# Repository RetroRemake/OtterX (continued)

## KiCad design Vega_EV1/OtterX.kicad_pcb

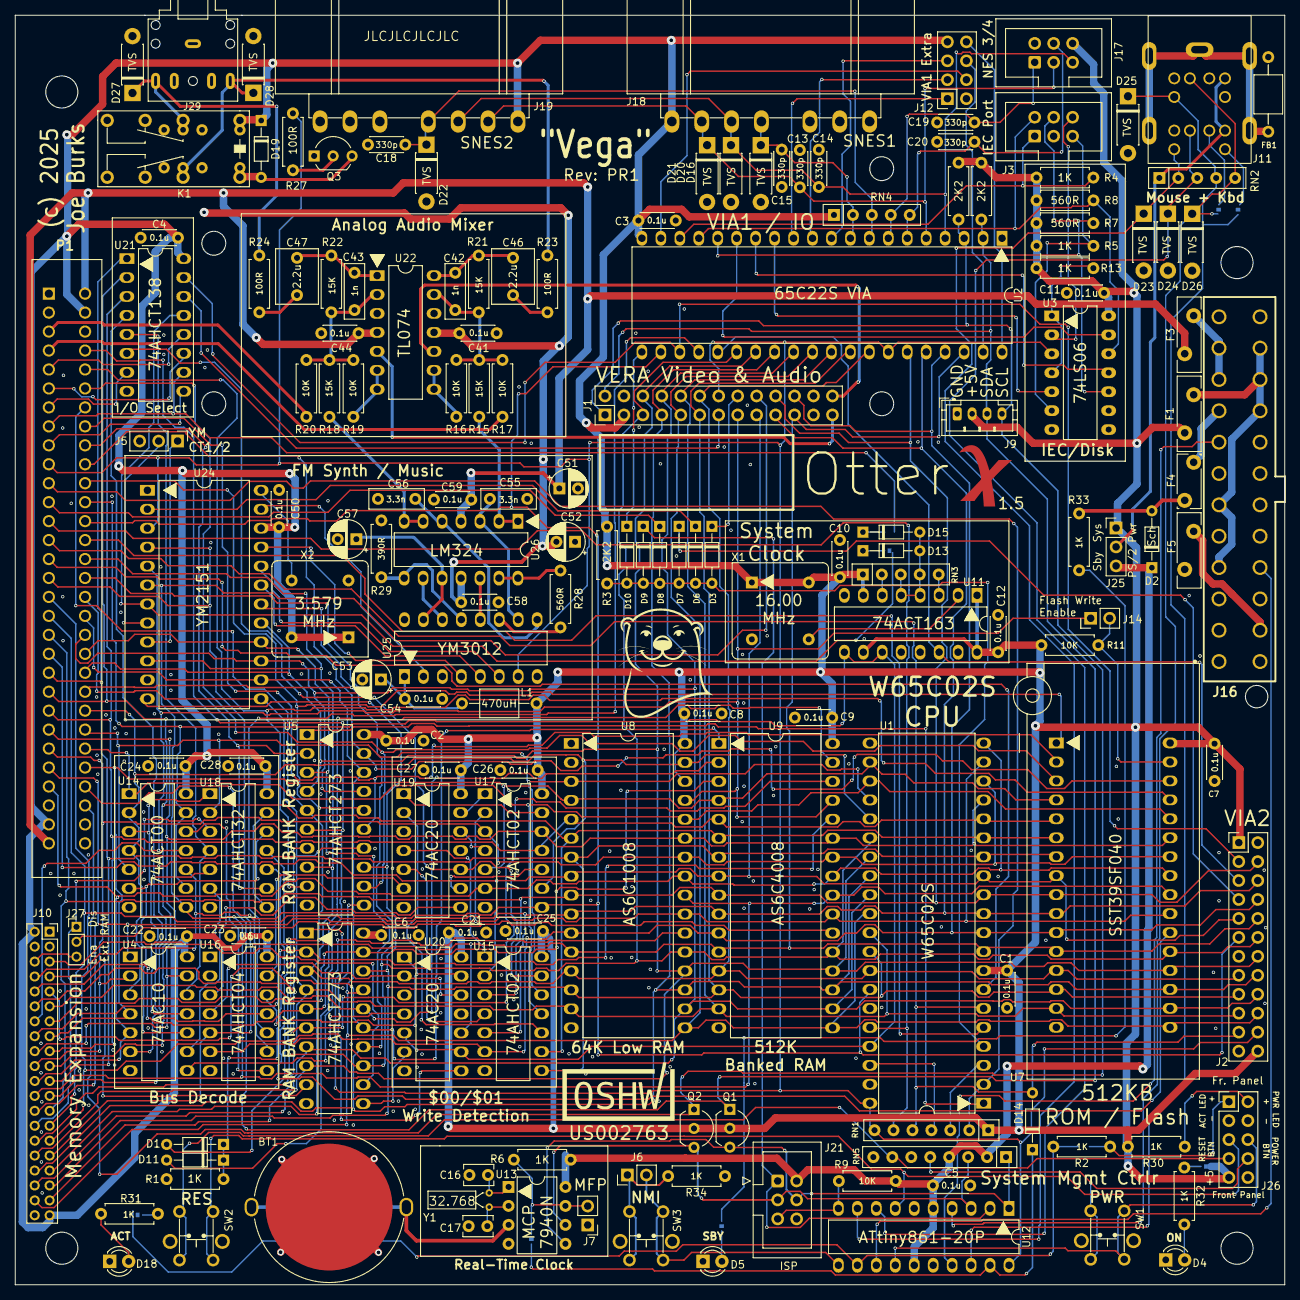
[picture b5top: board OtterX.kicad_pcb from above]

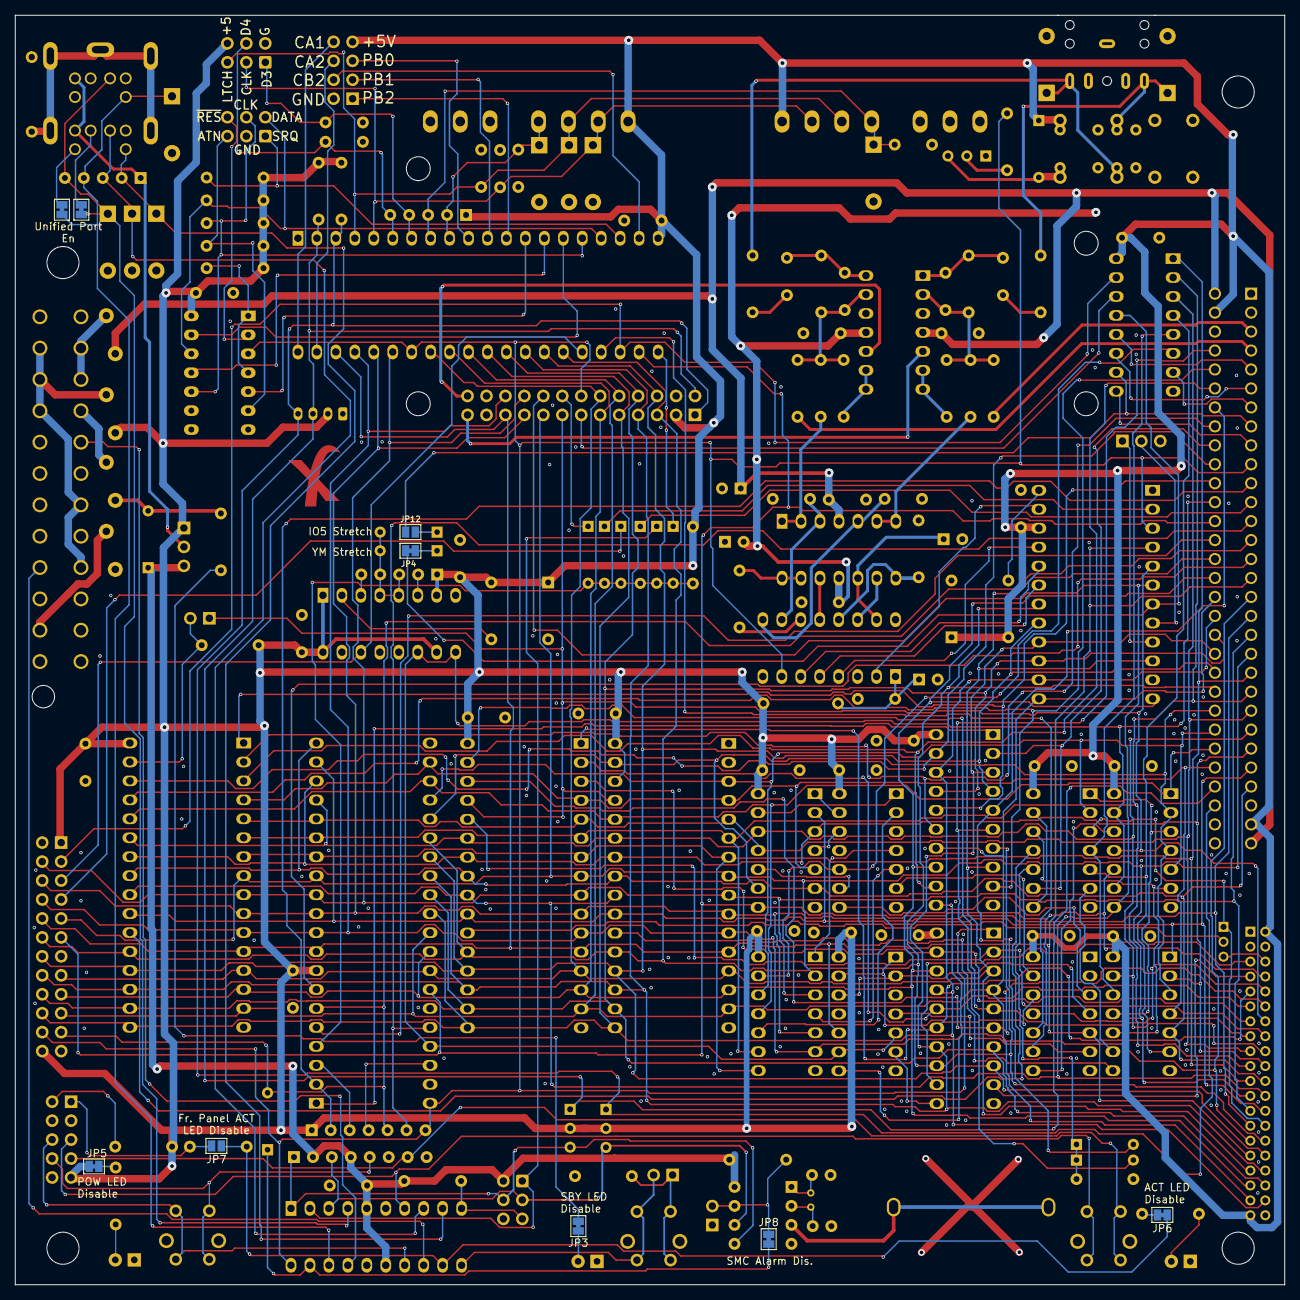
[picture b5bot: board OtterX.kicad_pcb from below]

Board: 4 copper layers, 170.1 x 170.1 mm, 185 parts (9 on the bottom side), 205 nets.

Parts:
BT1: BAT-HLD-001-THM; AliEx_BatClip
C1, C2, C3, C4, C5, C6, C7, C8, C9, C10, C11, C12, C21, C22, C23, C24, C25, C26, C27, C28, C41, C44, C50, C54, C58, C59: 0.1u; C_Disc_D4.3mm_W1.9mm_P5.00mm
C13, C14, C15, C18, C19, C20: 330p; C_Disc_D4.3mm_W1.9mm_P5.00mm
C16, C17: 3p; C_Disc_D3.8mm_W2.6mm_P2.50mm
C42, C43: 1n; C_Rect_L7.2mm_W2.5mm_P5.00mm_FKS2_FKP2_MKS2_MKP2
C46, C47: 2.2u; C_Rect_L7.2mm_W5.5mm_P5.00mm_FKS2_FKP2_MKS2_MKP2
C51, C52, C53, C57: 10u; CP_Radial_D5.0mm_P2.50mm
C55, C56: 3.3n; C_Rect_L7.2mm_W2.5mm_P5.00mm_FKS2_FKP2_MKS2_MKP2
D1, D3, D6, D7, D8, D9, D10, D11, D13, D14, D15, D19: 1N4148; D_DO-34_SOD68_P7.62mm_Horizontal
D2: 1N5819; D_DO-34_SOD68_P7.62mm_Horizontal
D4: LED_GRN; LED_D3.0mm
D5: LED_YEL; LED_D3.0mm
D16, D20, D21, D22, D23, D24, D25, D26, D27, D28: P4KE6.8CA; D_DO-41_SOD81_P7.62mm_Horizontal
D18: LED_RED; LED_D3.0mm
F1: JK30; Fuse_Bourns_MF-RG400
F3: RXEF110; Fuse_Bourns_MF-RG400
F4: RXEF025; Fuse_Bourns_MF-RG300
F5: RXEF010; Fuse_Bourns_MF-RG400
FB1: FerriteBead_Small; L_Axial_L5.0mm_D3.6mm_P10.00mm_Horizontal_Murata_BL01RN1A2A2
H1, H2, H3, H4: MountingHole; MountingHole_3.2mm_M3
H5, H6, H7, H8: MountingHole; MountingHole_4.3mm_M4
J1: VERA_CONN; PinHeader_2x13_P2.54mm_Vertical
J2: VIA2 Header; PinHeader_2x12_P2.54mm_Vertical
J3, J17, J21: IDC_2x03; IDC-Header_2x03_P2.54mm_Vertical
J5: YM CT Out; PinHeader_1x03_P2.54mm_Vertical
J6: Ext. NMI; PinHeader_1x02_P2.54mm_Vertical
J7: RTC GPIO; PinHeader_1x02_P2.54mm_Vertical
J9: I2C; JST_PH_B4B-PH-K_1x04_P2.00mm_Vertical
J10: 1.5MB RAM Expansion; PinSocket_2x20_P2.00mm_Vertical
J11: KMDGX-6SG; Kycon KMDGX-6SG P-S4N
J12: VIA1 Extra Pins; PinSocket_2x04_P2.54mm_Vertical
J14: Flash WR EN; PinHeader_1x02_P2.54mm_Vertical
J16: ATX-24; 1-1775099-3-Fixed
J18: SNES0; SNES_L
J19: SNES1; SNES_R
J25: PS2 Pwr Src; PinHeader_1x03_P2.54mm_Vertical
J26: Front Panel; PinHeader_2x05_P2.54mm_Vertical
J27: EXTRAM_ENABLE; PinHeader_1x03_P2.00mm_Vertical
J29: AudioPlug3; Jack_3.5mm_CUI_SJ1-3525N_Horizontal
JP1: SinglePS2_CLK; SolderJumper-2_P1.3mm_Bridged_Pad1.0x1.5mm
JP2: SinglePS2_DAT; SolderJumper-2_P1.3mm_Bridged_Pad1.0x1.5mm
JP3: SBY LED Disable; SolderJumper-2_P1.3mm_Bridged_Pad1.0x1.5mm
JP4: SolderJumper_2_Bridged; SolderJumper-2_P1.3mm_Bridged_Pad1.0x1.5mm
JP5: Pow LED Disable; SolderJumper-2_P1.3mm_Bridged_Pad1.0x1.5mm
JP6: Act LED Disable; SolderJumper-2_P1.3mm_Bridged_Pad1.0x1.5mm
JP7: ACT LED Bypass; SolderJumper-2_P1.3mm_Open_Pad1.0x1.5mm
JP8: SMC Alarm; SolderJumper-2_P1.3mm_Bridged_Pad1.0x1.5mm
JP12: IO3 Clk Stretch; SolderJumper-2_P1.3mm_Open_Pad1.0x1.5mm
K1: HK19F; HK19F-DPDT-Relay
L1: 470uH; L_Axial_L5.0mm_D3.6mm_P10.00mm_Horizontal_Murata_BL01RN1A2A2
P1: 60 Pin Edge Conn; TE155308438
Q1, Q2, Q3: 2N7000; TO-92_Inline_Wide
R1, R2, R4, R5, R6, R13, R30, R31, R32, R33, R34: 1K; R_Axial_DIN0207_L6.3mm_D2.5mm_P7.62mm_Horizontal
R3, R10, R12: 2K2; R_Axial_DIN0207_L6.3mm_D2.5mm_P7.62mm_Horizontal
R7, R8, R28: 560R; R_Axial_DIN0207_L6.3mm_D2.5mm_P7.62mm_Horizontal
R9, R11, R16, R17, R19, R20: 10K; R_Axial_DIN0207_L6.3mm_D2.5mm_P7.62mm_Horizontal
R15, R18, R21, R22: 15K; R_Axial_DIN0207_L6.3mm_D2.5mm_P7.62mm_Horizontal
R23, R24, R27: 100R; R_Axial_DIN0207_L6.3mm_D2.5mm_P7.62mm_Horizontal
R29: 390R; R_Axial_DIN0207_L6.3mm_D2.5mm_P7.62mm_Horizontal
RN1: 2K2; R_Array_SIP7
RN2, RN3: 2K2; R_Array_SIP5
RN4: 3K3; R_Array_SIP5
RN5: 2K2; R_Array_SIP8
SW1, SW2, SW3: FSM4JH; Tactile Switch Dual
U1: W65C816S; DIP-40_W15.24mm-ShortWidePads_1mmDrill
U2: W65C22S; DIP-40_W15.24mm-ShortWidePads_1mmDrill
U3: 74LS06; DIP-14_W7.62mm_ShortWidePads
U4: 74AC10; DIP-14_W7.62mm_ShortWidePads_Drill1mm
U5, U6: 74AHCT273; DIP-20_W7.62mm_ShortWidePads_1mmDrill
U7: SST39SF040; DIP_Socket-32_W11.9_W12.7_W15.24_W17.78_W18.5_3M_232-1285-0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
U8: AS6C1008-55PCN; DIP-32_W15.24mm_ShortWidePads_1mmDrill
U9: AS6C4008-55PCN; DIP-32_W15.24mm_ShortWidePads_1mmDrill
U11: 74ACT163; DIP-16_W7.62mm_ShortWidePads_1mmDrill
U12: ATtiny861-20P; DIP-20_W7.62mm_ShortWidePads_1mmDrill
U13: MCP7940N-xP; DIP-8_W7.62mm
U14: 74ACT00; DIP-14_W7.62mm_ShortWidePads_Drill1mm
U15, U17: 74AHCT02; DIP-14_W7.62mm_ShortWidePads_Drill1mm
U16: 74AHCT04; DIP-14_W7.62mm_ShortWidePads_Drill1mm
U18: 74AHCT32; DIP-14_W7.62mm_ShortWidePads_Drill1mm
U19, U20: 74AC20; DIP-14_W7.62mm_ShortWidePads_Drill1mm
U21: 74AHCT138; DIP-16_W7.62mm_ShortWidePads_1mmDrill
U22: TL074; DIP-14_W7.62mm_ShortWidePads_Drill1mm
U24: YM2151; DIP-24_W15.24mm_ShortWidePads_1mmDrill
U25: YM3012; DIP-16_W7.62mm_ShortWidePads_1mmDrill
U26: LM324; DIP-14_W7.62mm_ShortWidePads_Drill1mm
X1: ACH-16.000MHZ-EK; Oscillator_DIP-8
X2: ECS-2100AX-3.579545MHZ; Oscillator_DIP-8
Y1: ECS-.327-6-13X; Crystal_DS26_D2.0mm_L6.0mm_Horizontal

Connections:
+5V: C1.2, C2.2, C3.2, C4.2, C6.2, C7.2, C8.2, C9.2, C10.2, C11.2, C12.1, C21.1, C22.1, C23.1, C24.1, C25.1, C26.1, C27.1, C28.1, C50.2, D19.1 (K), F1.2, J1.3, J2.1, J2.24, J9.2, J10.2, J10.39, J12.7, J17.6, J18.1, J19.1, J25.1, J26.9, JP5.1 (A), K1.16, L1.1, P1.4 (VCC), P1.57 (VCC), Q1.2 (G), Q2.2 (G), R3.1, R4.1, R5.1, R7.1, R8.1, R10.1, R11.1, R12.1, R13.1, R30.2, RN1.1 (common), RN3.1 (common), RN4.1 (common), U1.8 (VDD), U2.20 (VCC), U3.14 (VCC), U4.14 (VCC), U5.20 (VCC), U6.20 (VCC), U7.32 (VCC), U8.30 (CE2), U8.32 (VCC), U9.32 (VCC), U11.1 (~MR), U11.7 (CEP), U11.10 (CET), U11.16 (VCC), U14.14 (VCC), U15.14 (VCC), U16.14 (VCC), U17.14 (VCC), U18.14 (VCC), U19.14 (VCC), U20.14 (VCC), U21.16 (VCC), U24.22 (Vcc), X1.1 (EN), X1.8 (Vcc), X2.1 (EN), X2.8 (Vcc)
+5VSB: C5.2, D2.1 (K), J21.2, J25.3, R6.2, R9.2, RN5.2 (R1.2), RN5.4 (R2.2), U12.5 (VCC), U12.15 (AVCC), U13.8 (VCC)
+5VSB_NOBF: D2.2 (A), F4.1, R33.1
+12V: C44.2, C51.1, C59.2, F3.1, P1.2 (+12V), P1.59 (+12V), U22.4 (V+), U26.4 (V+)
-12V: C41.2, C52.2, C58.2, F5.1, P1.1 (-12V), P1.60 (-12V), U22.11 (V-), U26.11 (V-)
/Audio/Audio Mixer/L_MIX: C43.1, R18.2, R19.2, R20.2, R22.1, U22.2 (-)
/Audio/Audio Mixer/L_P_FILT: C43.2, C47.1, R22.2, U22.1
/Audio/Audio Mixer/R_MIX: C42.1, R15.2, R16.2, R17.2, R21.1, U22.13 (-)
/Audio/Audio Mixer/R_P_FILT: C42.2, C46.1, R21.2, U22.14
/Audio/SH1: U24.20 (SH1), U25.6 (SH1)
/Audio/SH2: U24.19 (SH2), U25.5 (SH2)
/Audio/SO: U24.21 (SO), U25.4 (DATA)
/Audio/YMANL_5V: C53.1, C54.2, L1.2, U25.1 (Vcc)
/Audio/YMANL_CH1: C56.1, U25.9 (CH2), U26.5 (+)
/Audio/YMANL_CH2: C55.1, U25.10 (CH1), U26.3 (+)
/Audio/YMSAMP_OUT: U25.12 (T-BUF(A-OUT)), U26.12 (+)
/Audio/YMVREF_BIAS: C57.1, U25.15 (RB(BIAS)), U26.10 (+)
/Audio/YMVREF_IN: R29.1, U25.13 (MP(V/2)), U26.8
/Audio/YMVREF_OUT: U25.14 (BC(V/2)), U26.9 (-)
/Audio/YM_CLK: U24.24 (phM), X2.5 (OUT)
/Audio/YM_CLK2: U24.23 (phi1), U25.2 (phi1)
/Audio/YM_COM: R28.2, U25.11 (COM(A-IN))
/Audio/YM_CT1: J5.2, U24.8 (CT1)
/Audio/YM_CT2: J5.1, U24.9 (CT2)
/BusDecoder/~ROMENL: U4.10, U14.6, U18.12
/CLK16: U11.2 (CP), X1.5 (OUT)
/IECATT: J3.5, R5.2, U3.6
/IECSRQ: J3.1, R4.2, U2.18 (CB1)
/Memory/RAMBA13: J10.16, U6.2 (Q0), U9.28 (A13)
/Memory/RAMBA14: J10.13, U6.19 (Q7), U9.3 (A14)
/Memory/RAMBA15: J10.10, U6.5 (Q1), U9.31 (A15)
/Memory/RAMBA16: J10.11, U6.16 (Q6), U9.2 (A16)
/Memory/RAMBA17: J10.12, U6.6 (Q2), U9.30 (A17)
/Memory/RAMBA18: J10.9, U6.15 (Q5), U9.1 (A18)
/Memory/RAMBA19: J10.7, U6.9 (Q3)
/Memory/RAMBA20: J10.5, U6.12 (Q4)
/Memory/ROMBA14: P1.10 (ROMB0), U5.9 (Q3), U7.29 (A14)
/Memory/ROMBA15: P1.12 (ROMB1), U5.12 (Q4), U7.3 (A15)
/Memory/ROMBA16: P1.16 (ROMB2), U5.15 (Q5), U7.2 (A16)
/Memory/ROMBA17: P1.20 (ROMB3), U5.19 (Q7), U7.30 (A17)
/Memory/ROMBA18: P1.22 (ROMB4), U5.16 (Q6), U7.1 (A18)
/Memory/~BRAM_INT: J27.2, U9.22 (CE#)
/Memory/~FL_WE: J14.2, R11.2, U7.31 (PGM)
/SMC/5V0_UF: F1.1, J16.4 (+5V), J16.6 (+5V), J16.21 (+5V), J16.22 (+5V), J16.23 (+5V)
/SMC/5VSB_UF: F4.2, J16.9 (+5VSB)
/SMC/12V0_UF: F3.2, J16.10 (+12V), J16.11 (+12V)
/SMC/ACTLED: JP6.1 (A), JP7.1 (A), R2.1, U12.12 (PA6)
/SMC/BI_ACTLED: D18.2 (A), R31.2
/SMC/FP_ACTLED: J26.1, JP7.2 (B), R2.2
/SMC/FP_PWRLED: J26.2, R30.1
/SMC/N12V0_UF: F5.2, J16.14 (-12V)
/SMC/NMI_BTN: J6.2, SW3.1, U12.11 (PA7)
/SMC/POW_BTN: J26.6, SW1.1, U12.14 (PA4)
/SMC/POW_PD: J26.8, RN5.5 (R3.1), SW1.2
/SMC/RESBTN_PD: J26.7, RN5.7 (R4.1), SW2.2
/SMC/RES_BTN: J26.5, SW2.1, U12.7 (XTAL1/PB4)
/SMC/RTC_GPIO: J7.2, JP8.2 (B), R6.1, U13.7 (MFP)
/SMC/SMC_SCL: J21.3, Q2.3 (D), RN5.3 (R2.1), U12.3 (PB2), U13.6 (SCL)
/SMC/SMC_SDA: J21.4, Q1.3 (D), RN5.1 (R1.1), U12.1 (PB0), U13.5 (SDA)
/SMC/VBATT: BT1.1 (V+), U13.3 (VBAT)
/SMC/~SMC_NMI: D14.1 (K), JP8.1 (A), U12.19 (PA1)
/SMC/~SMC_RESET: J21.5, R9.1, U12.10 (~RESET/PB7)
/~IECRES: J3.6, U3.2
A0: J1.21, J2.10, J10.31, P1.31 (A0), U1.9 (A0), U2.38 (RS0), U7.12 (A0), U8.12 (A0), U9.12 (A0), U16.5, U20.10, U24.4 (A0)
A1: J1.22, J2.8, J10.29, P1.33 (A1), U1.10 (A1), U2.37 (RS1), U7.11 (A1), U8.11 (A1), U9.11 (A1), U15.6
A2: J1.19, J2.6, J10.27, P1.35 (A2), U1.11 (A2), U2.36 (RS2), U7.10 (A2), U8.10 (A2), U9.10 (A2), U15.5
A3: J1.20, J2.4, J10.25, P1.37 (A3), U1.12 (A3), U2.35 (RS3), U7.9 (A3), U8.9 (A3), U9.9 (A3), U15.3
A4: J1.17, J2.9, J10.23, P1.39 (A4), U1.13 (A4), U7.8 (A4), U8.8 (A4), U9.8 (A4), U15.2, U16.11
A5: J10.21, P1.41 (A5), U1.14 (A5), U7.7 (A5), U8.7 (A5), U9.7 (A5), U15.8, U21.1 (A0)
A6: J10.19, P1.43 (A6), U1.15 (A6), U7.6 (A6), U8.6 (A6), U9.6 (A6), U15.9, U21.2 (A1)
A7: J10.17, P1.45 (A7), U1.16 (A7), U7.5 (A7), U8.5 (A7), U9.5 (A7), U17.11, U21.3 (A2)
A8: J10.18, P1.47 (A8), U1.17 (A8), U4.13, U7.27 (A8), U8.27 (A8), U9.27 (A8), U17.12
A9: J10.20, P1.49 (A9), U1.18 (A9), U4.2, U7.26 (A9), U8.26 (A9), U9.26 (A9), U17.3
A10: J10.26, P1.51 (A10), U1.19 (A10), U4.1, U7.23 (A10), U8.23 (A10), U9.23 (A10), U17.2
A11: J10.22, P1.53 (A11), U1.20 (A11), U4.5, U7.25 (A11), U8.25 (A11), U9.25 (A11), U17.6
A12: J10.15, P1.52 (A12), U1.22 (A12), U4.4, U7.4 (A12), U8.4 (A12), U9.4 (A12), U17.5
A13: P1.50 (A13), U1.23 (A13), U7.28 (A13), U8.28 (A13), U14.1, U15.11
A14: P1.48 (A14), U1.24 (A14), U8.3 (A14), U14.5, U15.12, U18.2
A15: P1.46 (A15), U1.25 (A15), U4.3, U8.31 (A15), U14.2, U14.4, U17.9
BE: P1.25 (BE), RN1.6 (R5), U1.36 (BE)
BRAMLD: U6.11 (Cp), U20.6
BROMLD: U5.11 (Cp), U20.8
CA1: J12.8, U2.40 (CA1)
CA2: J12.6, U2.39 (CA2)
CARD_AUDIO_L: P1.5 (AUDIO_L), R20.1
CARD_AUDIO_R: P1.7 (AUDIO_R), R17.1
CB2: J12.4, U2.19 (CB2)
D0: J1.12, J2.15, J10.33, P1.30 (D0), U1.33 (D0), U2.33 (D0), U5.8 (D3), U6.3 (D0), U7.13 (D0), U8.13 (DQ0), U9.13 (DQ0), U24.10 (D0)
D1: J1.11, J2.17, J10.35, P1.32 (D1), U1.32 (D1), U2.32 (D1), U5.13 (D4), U6.18 (D7), U7.14 (D1), U8.14 (DQ1), U9.14 (DQ1), U24.12 (D1)
D2: J1.10, J2.19, J10.37, P1.34 (D2), U1.31 (D2), U2.31 (D2), U5.14 (D5), U6.4 (D1), U7.15 (D2), U8.15 (DQ2), U9.15 (DQ2), U24.13 (D2)
D3: J1.9, J2.20, J10.38, P1.36 (D3), U1.30 (D3), U2.30 (D3), U5.18 (D7), U6.17 (D6), U7.17 (D3), U8.17 (DQ3), U9.17 (DQ3), U24.14 (D3)
D4: J1.8, J2.18, J10.36, P1.38 (D4), U1.29 (D4), U2.29 (D4), U5.17 (D6), U6.7 (D2), U7.18 (D4), U8.18 (DQ4), U9.18 (DQ4), U24.15 (D4)
D5: J1.7, J2.16, J10.34, P1.40 (D5), U1.28 (D5), U2.28 (D5), U5.3 (D0), U6.14 (D5), U7.19 (D5), U8.19 (DQ5), U9.19 (DQ5), U24.16 (D5)
D6: J1.6, J2.14, J10.32, P1.42 (D6), U1.27 (D6), U2.27 (D6), U5.4 (D1), U6.8 (D3), U7.20 (D6), U8.20 (DQ6), U9.20 (DQ6), U24.17 (D6)
D7: J1.5, J2.12, J10.30, P1.44 (D7), U1.26 (D7), U2.26 (D7), U5.7 (D2), U6.13 (D4), U7.21 (D7), U8.21 (DQ7), U9.21 (DQ7), U24.18 (D7)
GND: BT1.2 (V-), C1.1, C2.1, C3.1, C4.1, C5.1, C6.1, C7.1, C8.1, C9.1, C10.1, C11.1, C12.2, C13.2, C14.2, C15.2, C16.2, C17.2, C18.2, C19.2, C20.2, C21.2, C22.2, C23.2, C24.2, C25.2, C26.2, C27.2, C28.2, C41.1, C44.1, C50.1, C51.2, C52.1, C53.2, C54.1, C55.2, C56.2, C57.2, C58.1, C59.1, D4.1 (K), D5.1 (K), D16.2 (A2), D18.1 (K), D20.2 (A2), D21.2 (A2), D22.2 (A2), D23.2 (A2), D24.2 (A2), D25.2 (A2), D26.2 (A2), D27.2 (A2), D28.2 (A2), FB1.2, J1.4, J1.23, J1.24, J2.2, J2.13, J2.23, J3.3, J5.3, J7.1, J9.1, J10.1, J10.40, J11.3, J11.9, J12.2, J16.3 (GND), J16.5 (GND), J16.7 (GND), J16.15 (GND), J16.17 (GND), J16.18 (GND), J16.19 (GND), J16.24 (GND), J17.2, J18.7, J19.7, J21.6, J26.3, J26.4, J29.S, K1.6, K1.11, P1.3 (GND), P1.6 (GND), P1.55 (GND), P1.58 (GND), Q3.1 (S), R1.2, R29.2, R34.1, RN5.6 (R3.2), RN5.8 (R4.2), U1.21 (VSS), U2.1 (VSS), U3.7 (GND), U3.9, U4.7 (GND), U5.10 (GND), U6.10 (GND), U7.16 (GND), U8.2 (A16), U8.16 (VSS), U9.16 (VSS), U11.8 (GND), U12.6 (GND), U12.16 (AGND), U13.4 (VSS), U14.7 (GND), U15.7 (GND), U16.1, U16.7 (GND), U17.7 (GND), U18.7 (GND), U19.7 (GND), U20.7 (GND), U21.8 (GND), U22.3 (+), U22.12 (+), U24.1 (D-GND), U24.11 (A-GND), U25.3 (D-GND), U25.8 (A-GND), U25.16 (A-GND), X1.4 (GND), X2.4 (GND)
IECATTO: U2.13 (PB3), U3.5
IECCLK: J3.4, R7.2, U2.16 (PB6), U3.10
IECCLKO: U2.14 (PB4), U3.11
IECDATA: J3.2, R8.2, U2.17 (PB7), U3.12
IECDATAO: U2.15 (PB5), U3.13
L_AUDIO_OUT: D27.1 (A1), J29.T, K1.13, R24.2
MX: RN1.4 (R3), U1.38 (MX)
NESCLK: C13.1, D21.1 (A1), J17.3, J18.2, J19.2, U2.5 (PA3)
NESDAT0: C15.1, D16.1 (A1), J18.4, RN4.2 (R1), U2.9 (PA7)
NESDAT1: C18.1, D22.1 (A1), J19.4, RN4.3 (R2), U2.8 (PA6)
NESDAT2: C19.1, J17.1, RN4.4 (R3), U2.7 (PA5)
NESDAT3: C20.1, J17.4, RN4.5 (R4), U2.6 (PA4)
NESLATCH: C14.1, D20.1 (A1), J17.5, J18.3, J19.3, U2.4 (PA2)
unnamed: C46.2, R23.1
unnamed: C47.2, R24.1
unnamed: D1.1 (K), D11.1 (K), R1.1, U18.10
unnamed: D4.2 (A), R32.2
unnamed: D5.2 (A), JP3.2 (B)
unnamed: D13.2 (A), D15.2 (A), RN3.3 (R2), RN3.4 (R3), U11.4 (D1), U11.5 (D2)
unnamed: D13.1 (K), JP4.2 (B)
unnamed: D15.1 (K), JP12.1 (A)
unnamed: D19.2 (A), K1.1, Q3.3 (D)
unnamed: J6.1, R34.2, SW3.2
unnamed: FB1.1, J11.MH (Shield)
unnamed: J11.12, JP1.2 (B)
unnamed: J11.8, JP2.2 (B)
unnamed: JP3.1 (A), R33.2
unnamed: JP5.2 (B), R32.1
unnamed: JP6.2 (B), R31.1
unnamed: Q3.2 (G), R27.2
unnamed: R13.2, U3.1, U3.4
unnamed: RN3.2 (R1), U11.6 (D3)
unnamed: RN3.5 (R4), U11.3 (D0)
unnamed: C16.1, U13.1 (X1), Y1.1
unnamed: C17.1, U13.2 (X2), Y1.2
unnamed: U4.11, U14.3, U18.1
unnamed: U15.1, U19.4
unnamed: U15.4, U19.5
unnamed: U15.10, U19.2
unnamed: U16.3, U19.8
unnamed: U16.4, U20.2, U20.12
unnamed: U16.12, U20.1, U20.13
unnamed: U16.13, U19.6
unnamed: U17.1, U19.13
unnamed: U17.4, U19.12
unnamed: U17.10, U19.9
unnamed: U17.13, U19.1
unnamed: U4.9, U18.6
unnamed: U18.8, U18.13
unnamed: R19.1, U22.6 (-), U22.7
unnamed: R16.1, U22.8, U22.9 (-)
unnamed: R28.1, U26.13 (-), U26.14
PG1: U15.13, U19.10, U21.6 (E3)
PHI2: P1.24 (PHI2), U1.37 (ϕ0), U11.9 (~PE), U11.11 (Q3), U14.9, U14.13, U20.5, U20.9
PS2K_CLK: D25.1 (A1), J11.5, JP1.1 (A), RN2.4 (R3), U12.18 (PA2)
PS2K_DAT: D26.1 (A1), J11.1, JP2.1 (A), RN2.5 (R4), U12.4 (PB3)
PS2M_CLK: D23.1 (A1), J11.11, RN2.2 (R1), U12.9 (PB6)
PS2M_DAT: D24.1 (A1), J11.7, RN2.3 (R2), U12.8 (XTAL2/PB5)
PS2_PWR: J11.4, J11.10, J25.2, RN2.1 (common)
PWR_OK: J16.8 (PWR_OK), U12.17 (AREF/PA3)
RDY: P1.21 (RDY), RN1.2 (R1), U1.2 (RDY)
ROMBA19: P1.18 (ROMB5), U5.2 (Q0), U18.9
ROMBA20: D1.2 (A), P1.14 (ROMB6), U5.5 (Q1)
ROMBA21: D11.2 (A), P1.8 (ROMB7), U5.6 (Q2)
R_AUDIO_OUT: D28.1 (A1), J29.R, K1.4, R23.2
SCL: J1.1, J9.4, P1.56 (SCL), Q2.1 (S), R10.2, U2.3 (PA1)
SDA: J1.2, J9.3, P1.54 (SDA), Q1.1 (S), R12.2, U2.2 (PA0)
SYNC: P1.29 (SYNC), U1.7 (VPA)
V1PB0: J12.5, U2.10 (PB0)
V1PB1: J12.3, U2.11 (PB1)
V1PB2: J12.1, U2.12 (PB2)
VERA_AUDIO_L: J1.25, U22.5 (+)
VERA_AUDIO_R: J1.26, U22.10 (+)
VIACLK: J2.5, U2.25 (ϕ2), U11.14 (Q0)
YM_AUDIO_L: R18.1, U26.6 (-), U26.7
YM_AUDIO_R: R15.1, U26.1, U26.2 (-)
~A0: U16.6, U20.4
~A4: U2.24 (CS1), U16.10
~ABORT: RN1.3 (R2), U1.3 (~ABORT)
~BRAMEN0: J10.6, J27.3
~BRAMEN: J10.28, J27.1, U18.3
~EXP_IRQ: D8.1 (K), P1.23 (IRQB)
~IO3: P1.9 (/IO3), U21.12 (O3)
~IO4: P1.11 (/IO4), U21.11 (O4)
~IO5: JP12.2 (B), P1.15 (/IO5), U21.10 (O5)
~IO6: P1.17 (/IO6), U21.9 (O6)
~IO7: P1.13 (/IO7), U21.7 (O7)
~IRQ: D3.2 (A), D6.2 (A), D7.2 (A), D8.2 (A), D9.2 (A), D10.2 (A), R3.2, U1.4 (~IRQ)
~ML: P1.28 (MLB), U1.5 (~ML)
~NMI: D14.2 (A), J2.21, P1.27 (NMIB), RN1.5 (R4), U1.6 (~NMI)
~PG2A: U4.12, U18.4, U21.5 (E2)
~PG2B: U4.6, U18.5, U21.4 (E1)
~PS_ON: J16.16 (PS_ON#), U12.13 (PA5)
~RAMEN: U4.8, U8.22 (CE#)
~RES: J1.14, J2.22, P1.19 (/RESB), R27.1, RN1.7 (R6), U1.40 (~RES), U2.34 (~RES), U3.3, U6.1 (~Mr), U12.20 (PA0), U24.3 (~IC), U25.7 (~IC)
~RE: J1.18, J10.24, U7.24 (OE), U8.24 (OE#), U9.24 (OE#), U14.8, U24.6 (~RD)
~ROMEN: U7.22 (CE), U18.11
~RWB: J2.11, J10.8, P1.26 (RWB), U1.34 (R/~W), U2.22 (R/~W), U14.10, U16.9, U17.8
~SMC_IRQ: D9.1 (K), J21.1, U12.2 (PB1)
~VERA_CS: J1.13, U21.14 (O1)
~VERA_IRQ: D3.1 (K), J1.16
~VIA1_IRQ: D10.1 (K), U2.21 (~IRQ)
~VIA2_IRQ: D7.1 (K), J2.7
~VIA_CS: J2.3, U2.23 (~CS2), U21.15 (O0)
~VP: U1.1 (~VP), U5.1 (~Mr)
~WE: J1.15, J10.14, J14.1, U8.29 (WE#), U9.29 (WE#), U14.11, U24.5 (~WR)
~WRB: U14.12, U16.8
~YM_CS: JP4.1 (A), U21.13 (O2), U24.7 (~CS)
~YM_IRQ: D6.1 (K), U24.2 (~IRQ)

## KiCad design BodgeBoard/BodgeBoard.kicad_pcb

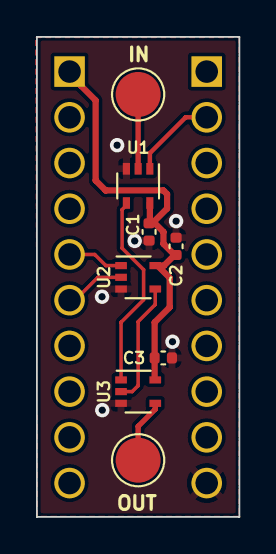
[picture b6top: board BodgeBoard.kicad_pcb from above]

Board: 2 copper layers, 11.2 x 26.7 mm, 10 parts (0 on the bottom side), 9 nets.

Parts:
C1, C2, C3: C; C_0402_1005Metric
J1, J2: Conn_01x10_Pin; PinHeader_1x10_P2.54mm_Vertical
TP1: ~{ROMEN}; TestPoint_Pad_D2.5mm
TP2: ~{ROM0EN}; TestPoint_Pad_D2.5mm
U1, U2: SN74AHC1G02DCKR; SOT-353_SC-70-5
U3: SN74AHC1G00DCKR; SOT-353_SC-70-5

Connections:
+5V: C1.1, C2.1, C3.1, J1.1, U1.5 (VCC), U2.5 (VCC), U3.5 (VCC)
/ROMBA19: J1.6, U2.2
/ROMBA20: J2.2, U1.1
/ROMBA21: J1.5, U2.1
/~ROM0EN: TP2.1, U3.4
/~ROMEN: TP1.1, U1.2
GND: C1.2, C2.2, C3.2, J2.10, U1.3 (GND), U2.3 (GND), U3.3 (GND)
unnamed: U1.4, U3.1
unnamed: U2.4, U3.2

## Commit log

2025-04-19 New open source repo
2025-04-20 Add memory expansion module
2025-04-20 Fix 3D models
2025-05-18 Fixes for #1 #2 #3 #4 #5 #6 #7 #8 #10 #11 #14
2025-06-14 Fix #16, widen transistor footprints
2025-07-03 Misc layout fixes.
2025-07-12 Add IEC circuit back in, without the port.
2025-07-15 More space between Edge and YM2151 Add IEC logic back in IDC headers for NES and IEC
2025-07-16 Add dongle boards and new battery clip
2025-07-22 Change 2.2u cap footprint; update MemoryExpansion
2025-07-23 Vega production Gerber Out
2025-07-23 Add IEC Dongle design
2025-11-05 Rename dongle boards to D'Otterboards
2026-06-11 Add missing items
2026-06-14 Revise where to buy section in README
    Updated purchase links for OtterX kits.
